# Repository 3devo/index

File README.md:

# Temporary fork of Index pick and place project

Forked by Jesse to scrap almost everything except for the kicad and kibot files.
Mainly to test Kibot integrated into Github Actions.

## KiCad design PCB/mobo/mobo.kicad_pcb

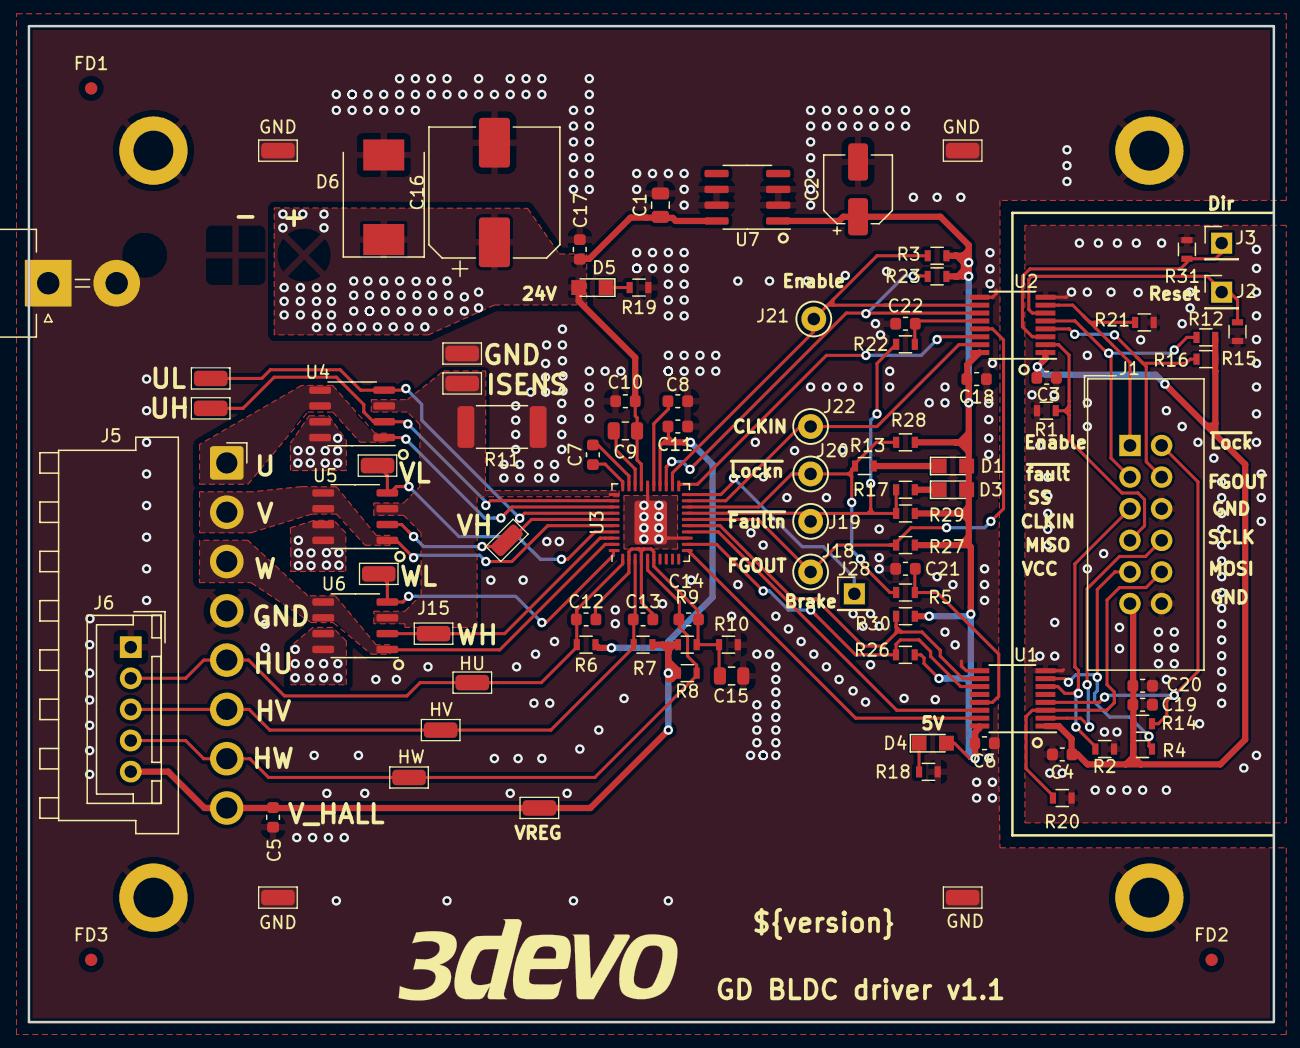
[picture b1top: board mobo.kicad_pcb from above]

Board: 2 copper layers, 100.0 x 80.0 mm, 99 parts (0 on the bottom side), 53 nets.

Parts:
C1, C9, C15: 1uF 35V; C_0805_2012Metric
C2: 22uF 35V; CP_Elec_5x5.8
C3, C4, C5, C6, C7, C10, C11, C12, C13, C14, C17, C18, C20, C21, C22: 100nF 50V; C_0603_1608Metric
C8, C19: 1uF 16V; C_0603_1608Metric
C16: 220uF 35V; CP_Elec_10x10
D1, D4, D5: Led_GREEN; LED_0805
D3: Led_RED; LED_0805
D6: 1.5SMC33CA-E3/57T; D_SMC
FD1, FD2, FD3: Fid; Fiducial_1mm_Mask2mm
H1, H2, H3, H4: MountingHole_Pad; MountingHole_3.2mm_M3_ISO14580_Pad
J1: Conn_02x06; IDC-Header_2x06_P2.54mm_Vertical
J2, J3, J28: CONN_01X01; PinHeader_1x01_P2.54mm_Vertical
J4, J7, J8, J9, J10, J11, J12, J13, J14, J15, J16, J17, J23, J24, J26, J27: TEST_1P; TestPoint_TE_RCT-0C_0805
J5: Conn_01x08; JST_VH_B8PS-VH_1x08_P3.96mm_Horizontal
J6: Conn_01x05_Female; JST_XH_B05B-XH-A_05x2.50mm_Straight
J18, J19, J20, J21, J22: TEST_1P; Test_Point_Keystone_5000-5004_Miniature
J25: Conn_01x02; Molex_MegaFit_2x01x5.70mm_Angled
R1, R2, R3, R5, R9, R10, R12, R14, R15, R16, R20, R21, R22, R23, R26, R27, R28, R29, R31: 10k; R_0603
R4, R6, R7, R8, R30: 2k2; R_0603
R11: 0R030; R_2512_6332Metric
R13, R17, R18: 1k; R_0603
R19: 4k7; R_0603
U1, U2: MAX14851; QSOP-16_3.9x4.9mm_P0.635mm
U3: DRV8308; Texas_S-PVQFN-N40_EP3.52x2.62mm
U4, U5, U6: CSD88537ND; SO-8_3.9x4.9mm_P1.27mm
U7: LM2931-5.0_SO8; SOIC-8_3.9x4.9mm_P1.27mm
X1: Logo; logo_3devo_23mm

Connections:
+5V: C2.1, C6.2, C18.2, D1.2, D3.2, D4.2, R3.2, R23.2, R26.2, R27.1, R28.1, R29.1, R30.2, U1.16, U2.16, U7.1
+24V: C1.1, C9.2, C10.1, C16.1, C17.1, D5.2, D6.1, J25.2, U3.27, U4.7, U4.8, U5.7, U5.8, U6.7, U6.8, U7.8
/BRAKE: J28.1, U3.20
/CLKIN: J22.1, U2.15, U3.19
/CLKIN_MCU: J1.7, R1.2, U2.2
/DIR: U2.14, U3.21
/DIR_MCU: J3.1, R31.2, U2.3
/ENABLE: J21.1, R3.1, U2.10, U3.22
/ENABLE_MCU: J1.1, R21.2, U2.7
/FGOUT: J18.1, R27.2, U2.13, U3.16
/FGOUT_MCU: J1.4, R16.2, U2.4
/MISO: R30.1, U1.10, U3.15
/MISO_MCU: J1.9, R4.1, U1.7
/MOSI: U1.14, U3.14
/MOSI_MCU: J1.10, R20.2, U1.3
/Reset: R23.1, U2.11, U3.23
/Reset_MCU: J2.1, R15.2, U2.6
/SCLK: U1.15, U3.11
/SCLK_MCU: J1.8, U1.2
/SS: R26.1, U1.11, U3.12
/SS_MCU: J1.5, R2.1, U1.6
/UHS_GATE: J7.1, U3.32, U4.2
/ULS_GATE: J8.1, U3.34, U4.4
/VHS_GATE: J9.1, U3.35, U5.2
/VLS_GATE: J10.1, U3.37, U5.4
/VREG: C5.2, C11.1, J5.8, J6.5, J14.1, R6.2, R7.2, R8.2, R9.2, U3.24
/WHS_GATE: J15.1, U3.38, U6.2
/WLS_GATE: J26.1, U3.40, U6.4
/~FAULTn_MCU: J1.3, R12.2, U2.5
/~FAULTn: J19.1, R17.2, R22.1, R29.2, U3.17
/~LOCKn_MCU: J1.2, R14.2, U1.4
/~LOCKn: J20.1, R5.1, R13.2, R28.2, U3.18
GND: C1.2, C2.2, C5.1, C6.1, C8.1, C10.2, C11.2, C15.2, C16.2, C17.2, C18.1, C21.1, C22.1, D6.2, H1.1, H2.1, H3.1, H4.1, J5.4, J6.1, J16.1, J17.1, J23.1, J24.1, J25.1, J27.1, R10.1, R11.1, R18.2, R19.2, U1.9, U2.9, U3.13, U3.26, U3.41, U7.2, U7.3, U7.6, U7.7
GNDA: C3.2, C4.2, C19.1, C20.1, J1.6, J1.12, R1.1, R2.2, R15.1, R20.1, R21.1, R31.1, U1.8, U2.8
HU: C12.1, J5.5, J6.2, J11.1, R6.1, U3.1
HV: C13.1, J5.6, J6.3, J12.1, R7.1, U3.3
HW: C14.1, J5.7, J6.4, J13.1, R8.1, U3.5
ISENSE: J4.1, R11.2, U3.31, U4.3, U5.3, U6.3
unnamed: C7.1, U3.30
unnamed: C7.2, U3.29
unnamed: C8.2, U3.25
unnamed: C9.1, U3.28
unnamed: C12.2, C13.2, C14.2, C15.1, R9.1, R10.2, U3.2, U3.4, U3.6
unnamed: C21.2, R5.2, U1.13
unnamed: C22.2, R22.2, U2.12
unnamed: D1.1, R13.1
unnamed: D3.1, R17.1
unnamed: D4.1, R18.1
unnamed: D5.1, R19.1
U: J5.1, U3.33, U4.1, U4.5, U4.6
V: J5.2, U3.36, U5.1, U5.5, U5.6
VCC: C3.1, C4.1, C19.2, C20.2, J1.11, R4.2, R12.1, R14.1, R16.1, U1.1, U2.1
W: J5.3, U3.39, U6.1, U6.5, U6.6

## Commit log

2022-03-09 Add manual dispatch option
2022-03-09 Remove redundant triggers and redundant pcb's
    Remove push/PR triggers
    Remove all pcb results except mobo
2022-03-09 Remove all files except for KiCad and KiBot
2022-03-09 Remove redundant workflow actions
2022-03-09 Update workflow
    String replace test
2022-03-09 Update workflow
    Remove clutter
2022-03-09 Only attach result to release if possible
2022-03-09 Try out gerber option
2022-03-09 Gerber correct case and put in folder
2022-03-09 Update case
2022-03-09 Update naming and folder structure
2022-03-09 Add paste layer to gerber export
2022-03-09 Remove redundant kibot and git files
2022-03-09 Remove tab in paste section
2022-03-10 Change bom from kibot to kibom
2022-03-10 Add kibom configuration file
2022-03-10 Add extra kibom ini file in pcb folder to test
2022-03-10 Add manufacturer and partnumber field
2022-03-10 add manu and partnr to global field template
2022-03-11 Add @version@ in silkscreen
2022-03-11 Add extra test yaml files
    - To test out full options of kibot
2022-03-11 Add example links
2022-03-15 Add test text_variables in layout
2022-03-15 Test version replacement in title block
2022-03-16 Local devcontainer working
2022-03-16 Remove stringreplacement, add timezone
2022-03-17 Modify gitignore
    Remove export folder from git
2022-03-17 Clean up, working
2022-03-28 Reset to state at 19c8c0d4
2022-04-19 Cleanup files and add kicad_libraries submodule
2022-04-19 Date/rev added correctly to kicad 6 files
2022-04-19 Pretty stable naming and xlsx output
2022-04-20 Stable XLSX export, print sch experiment
2022-04-20 Pretty stable full working config
